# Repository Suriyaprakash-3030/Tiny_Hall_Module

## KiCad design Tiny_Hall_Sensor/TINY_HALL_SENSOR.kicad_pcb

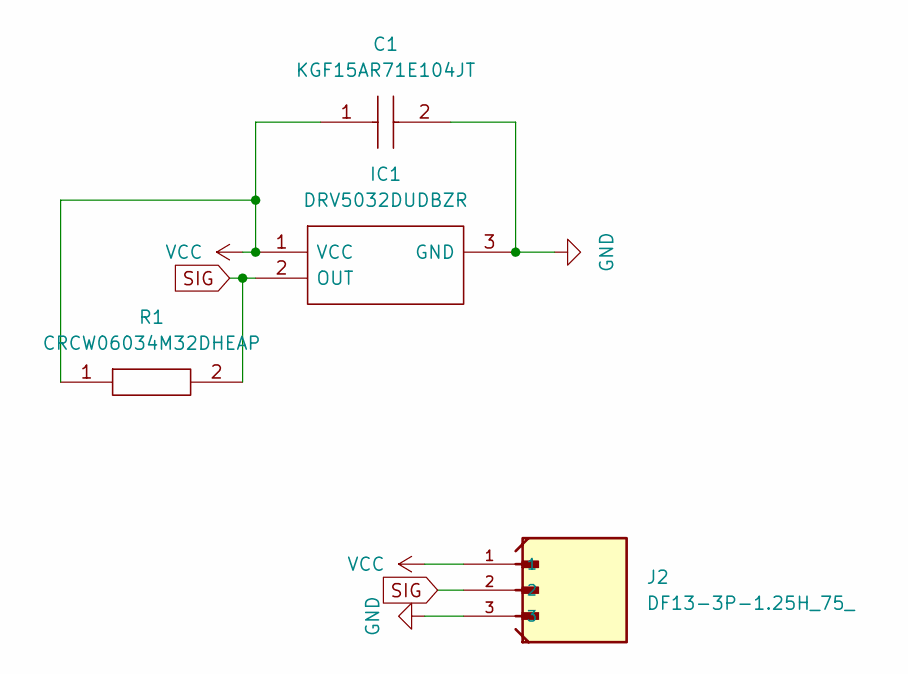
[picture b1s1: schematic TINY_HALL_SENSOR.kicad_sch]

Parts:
C1: KGF15AR71E104JT; CAPC1608X90N; Mouser Part Number 581-KGF15AR71E104JT
IC1: DRV5032DUDBZR; SOT95P237X112-3N; Mouser Part Number 595-DRV5032DUDBZR
J2: DF13-3P-1.25H_75_; HRS_DF13-3P-1.25H_75_
R1: CRCW06034M32DHEAP; RESC1608X50N; Mouser Part Number 71-CRCW06034M32DHEAP

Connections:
GND: C1.2, IC1.3 (GND), J2.3, J2.S1, J2.S2
SIG: IC1.2 (OUT), J2.2, R1.2
VCC: C1.1, IC1.1 (VCC), J2.1, R1.1

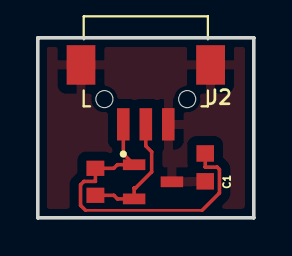
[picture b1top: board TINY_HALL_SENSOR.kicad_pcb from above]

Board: 2 copper layers, 12.0 x 10.0 mm, 4 parts (0 on the bottom side), 3 nets.

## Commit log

2024-12-09 Tiny hall sensor gerber and job file
2024-12-09 images added
